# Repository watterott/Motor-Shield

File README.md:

# Motor-Shield
Shield for Arduino to drive DC-Motors, Solenoids or Relays.

* Compatible with [Arduino Motor-Shield](https://www.arduino.cc/en/Main/ArduinoMotorShieldR3)
* ST L298 Dual Full-Bridge Driver (2A per channel or 4A max)
* Open-Source and released under the [Creative Commons Attribution Share-Alike License](https://creativecommons.org/licenses/by-sa/4.0/).
* **[Documentation on learn.watterott.com](https://learn.watterott.com)**

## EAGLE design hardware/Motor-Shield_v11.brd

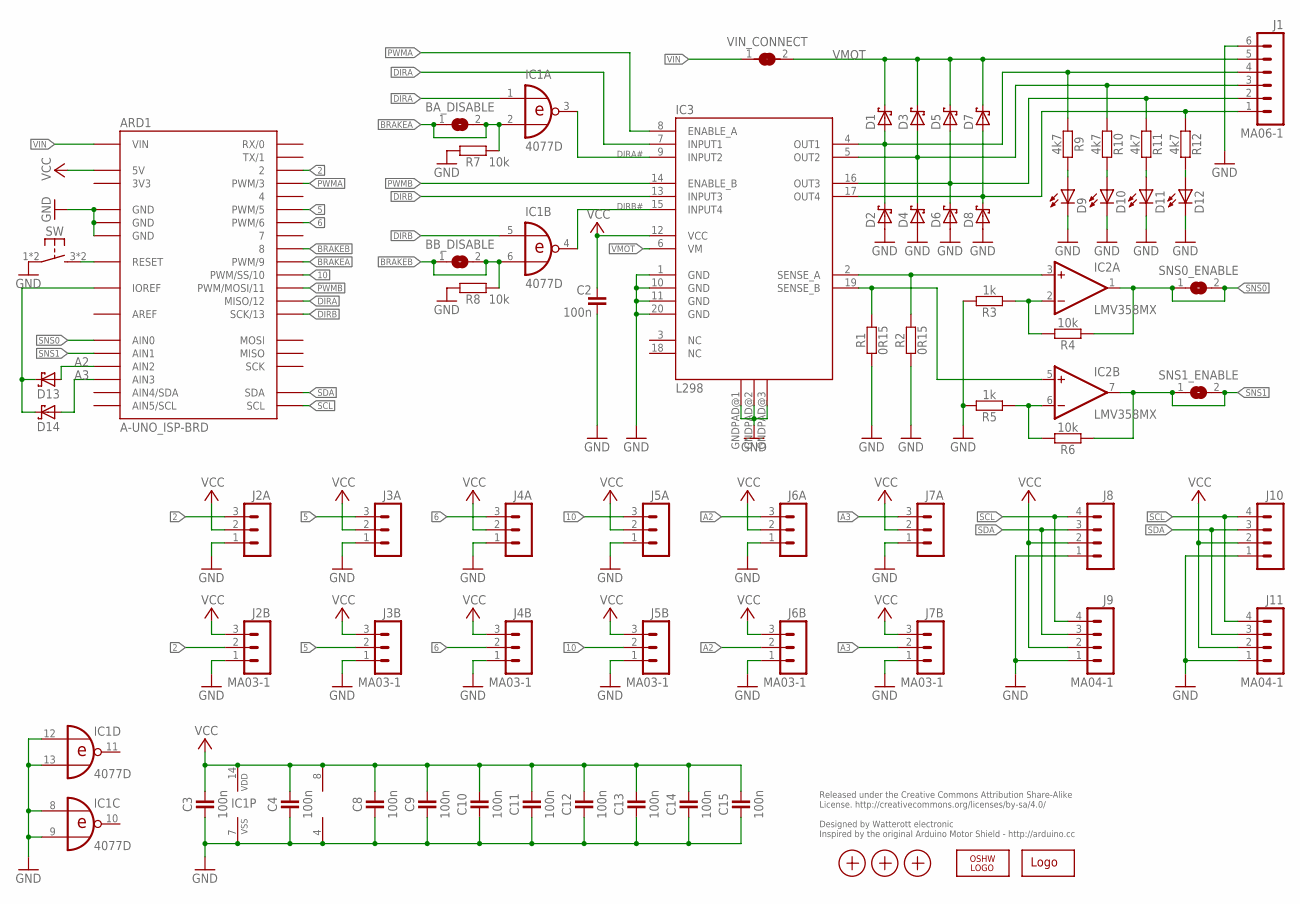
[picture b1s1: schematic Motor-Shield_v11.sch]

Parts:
ARD1: A-UNO_ISP-BRD; A-UNO-ISP
BA_DISABLE: JUMPER2-0603
BB_DISABLE: JUMPER2-0603
C2, C3, C4, C8, C9, C10, C11, C12, C13, C14, C15: 100n; C0402
D1, D2, D3, D4, D5, D6, D7, D8: D_SS14; DO214AC
D9, D10, D11, D12: LED-0603; C0603
D13, D14: D_SCHOTTKY-SOD110; SOD110
IC1: 4077D; SO14
IC2: LMV358MX; SO08
IC3: L298; POWERSO20
J1: MA06-1
J2A, J3A, J4A, J5A, J6A, J7A: JST_PH_3B3B-PH-SM4-TB; JST_B3B-PH-SM4-TB
J2B, J3B, J4B, J5B, J6B, J7B: MA03-1
J8, J10: JST_PH_4B4B-PH-SM4-TB; JST_B4B-PH-SM4-TB
J9, J11: MA04-1
LOGO1: LOGO-S_PLACE_S; SPARK_TPLACE_S
LOGO2: OSHW_LOGOX0070; OSHW_6X70
R1, R2: 0R15; C1206
R3, R5: 1k; C0402
R4, R6, R7, R8: 10k; C0402
R9, R10, R11, R12: 4k7; C0402
SNS0_ENABLE, SNS1_ENABLE: JUMPER2-0603
SW: SW-TACTILE-6X6_SMD; SW6X6_SMD
VIN_CONNECT: JUMPER2-0603
X1, X2, X3: PASSER-07; PASSER_07MM

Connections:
2: ARD1.2, J2A.3, J2B.2
3V3: ARD1.3V3
5: ARD1.5 (PWM/5), J3A.3, J3B.2
6: ARD1.6 (PWM/6), J4A.3, J4B.2
10: ARD1.10 (PWM/SS/10), J5A.3, J5B.2
A2: ARD1.A2 (AIN2), D13.A, J6A.3, J6B.2
A3: ARD1.A3 (AIN3), D14.A, J7A.3, J7B.2
AREF: ARD1.AREF
BRAKEA: ARD1.9 (PWM/9), BA_DISABLE.1, BA_DISABLE.2, IC1.2 (I1), R7.1
BRAKEB: ARD1.8, BB_DISABLE.1, BB_DISABLE.2, IC1.6 (I1), R8.1
DIRA: ARD1.12 (MISO/12), IC1.1 (I0), IC3.7 (INPUT1)
DIRA#: IC1.3 (O), IC3.9 (INPUT2)
DIRB: ARD1.13 (SCK/13), IC1.5 (I0), IC3.13 (INPUT3)
DIRB#: IC1.4 (O), IC3.15 (INPUT4)
GND: ARD1.GND@1 (GND), ARD1.GND@2 (GND), ARD1.GND@3 (GND), ARD1.GND@4 (GND), C2.1, C3.1, C4.1, C8.1, C9.1, C10.1, C11.1, C12.1, C13.1, C14.1, C15.1, D2.1 (A), D4.1 (A), D6.1 (A), D8.1 (A), D9.C, D10.C, D11.C, D12.C, IC1.7 (VSS), IC1.8 (I0), IC1.9 (I1), IC1.12 (I0), IC1.13 (I1), IC2.4 (V-), IC3.1 (GND), IC3.10 (GND), IC3.11 (GND), IC3.20 (GND), IC3.GNDPAD@1 (GNDPAD), IC3.GNDPAD@2 (GNDPAD), IC3.GNDPAD@3 (GNDPAD), J1.6, J2A.1, J2B.1, J3A.1, J3B.1, J4A.1, J4B.1, J5A.1, J5B.1, J6A.1, J6B.1, J7A.1, J7B.1, J8.1, J9.1, J10.1, J11.1, R1.1, R2.1, R3.2, R5.2, R7.2, R8.2, SW.1, SW.2 (P1)
IOREF: ARD1.IOREF, D13.C, D14.C
unnamed: D9.A, R9.2
unnamed: D10.A, R10.2
unnamed: IC2.2 (-IN), R3.1, R4.2
unnamed: IC2.6 (-IN), R5.1, R6.2
unnamed: D11.A, R11.2
unnamed: D12.A, R12.2
unnamed: ARD1.RST@1 (RESET), ARD1.RST@2 (RESET), SW.3 (S1), SW.4 (S1)
OUT1: D1.1 (A), D2.2 (C), IC3.4 (OUT1), J1.4, R9.1
OUT2: D3.1 (A), D4.2 (C), IC3.5 (OUT2), J1.3, R10.1
OUT3: D5.1 (A), D6.2 (C), IC3.16 (OUT3), J1.2, R11.1
OUT4: D7.1 (A), D8.2 (C), IC3.17 (OUT4), J1.1, R12.1
PWMA: ARD1.3 (PWM/3), IC3.8 (ENABLE_A)
PWMB: ARD1.11 (PWM/MOSI/11), IC3.14 (ENABLE_B)
SCL: ARD1.SCL, J8.4, J9.4, J10.4, J11.4
SDA: ARD1.SDA, J8.3, J9.3, J10.3, J11.3
SENSE_A: IC2.3 (+IN), IC3.2 (SENSE_A), R2.2
SENSE_B: IC2.5 (+IN), IC3.19 (SENSE_B), R1.2
SNS0: ARD1.A0 (AIN0), IC2.1 (OUT), R4.1, SNS0_ENABLE.1, SNS0_ENABLE.2
SNS1: ARD1.A1 (AIN1), IC2.7 (OUT), R6.1, SNS1_ENABLE.1, SNS1_ENABLE.2
VCC: ARD1.5V, ARD1.VCC (5V), C2.2, C3.2, C4.2, C8.2, C9.2, C10.2, C11.2, C12.2, C13.2, C14.2, C15.2, IC1.14 (VDD), IC2.8 (V+), IC3.12 (VCC), J2A.2, J2B.3, J3A.2, J3B.3, J4A.2, J4B.3, J5A.2, J5B.3, J6A.2, J6B.3, J7A.2, J7B.3, J8.2, J9.2, J10.2, J11.2
VIN: ARD1.VIN, VIN_CONNECT.1
VMOT: D1.2 (C), D3.2 (C), D5.2 (C), D7.2 (C), IC3.6 (VM), J1.5, VIN_CONNECT.2

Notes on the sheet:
Released under the Creative Commons Attribution Share-Alike License. http://creativecommons.org/licenses/by-sa/4.0/ Designed by Watterott electronic Inspired by the original Arduino Motor Shield - http://arduino.cc

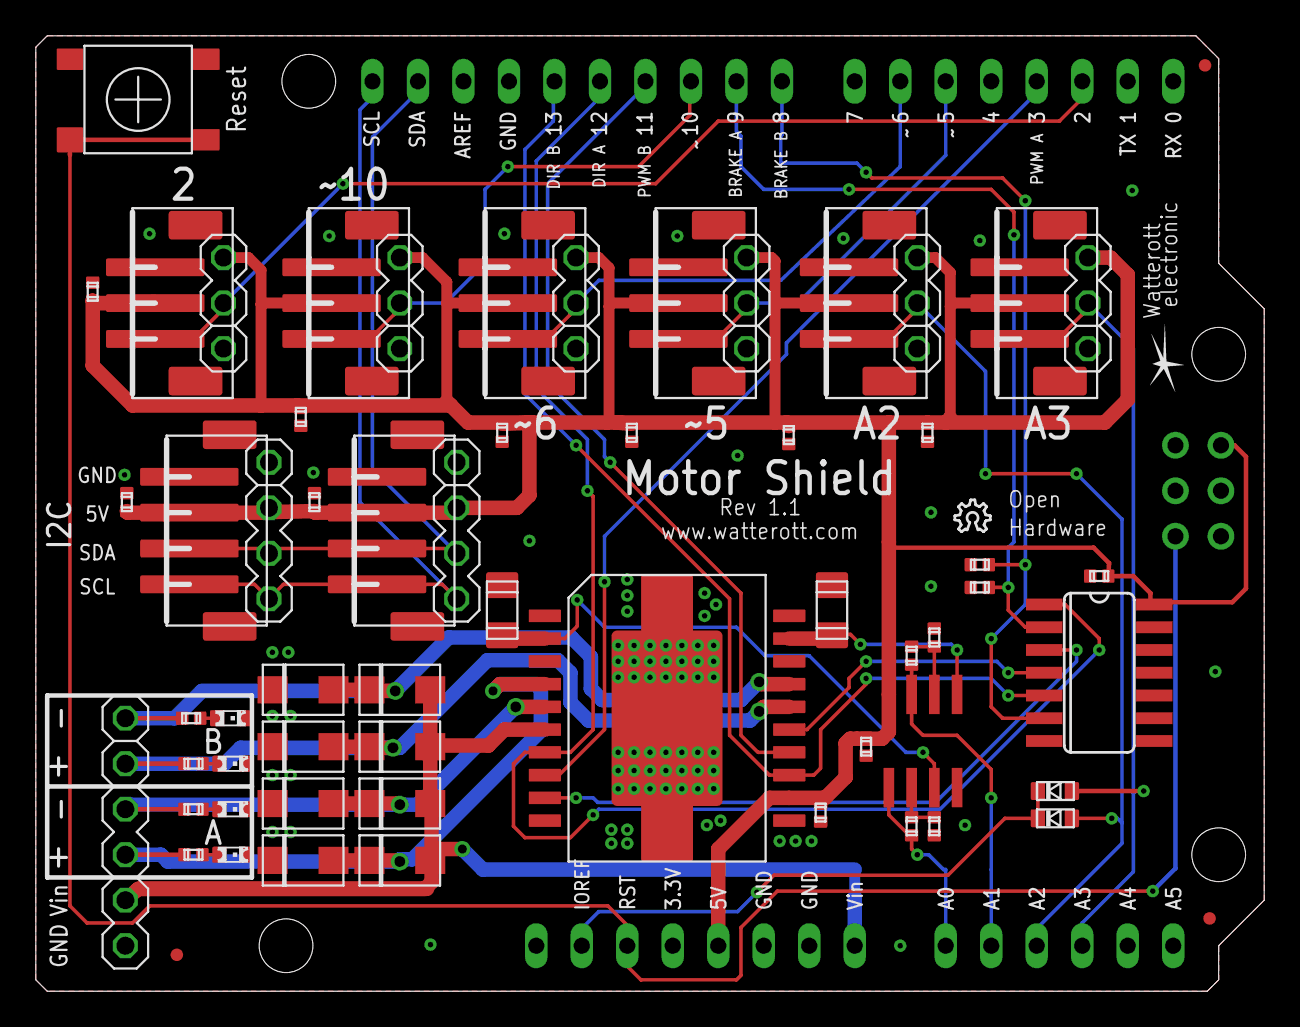
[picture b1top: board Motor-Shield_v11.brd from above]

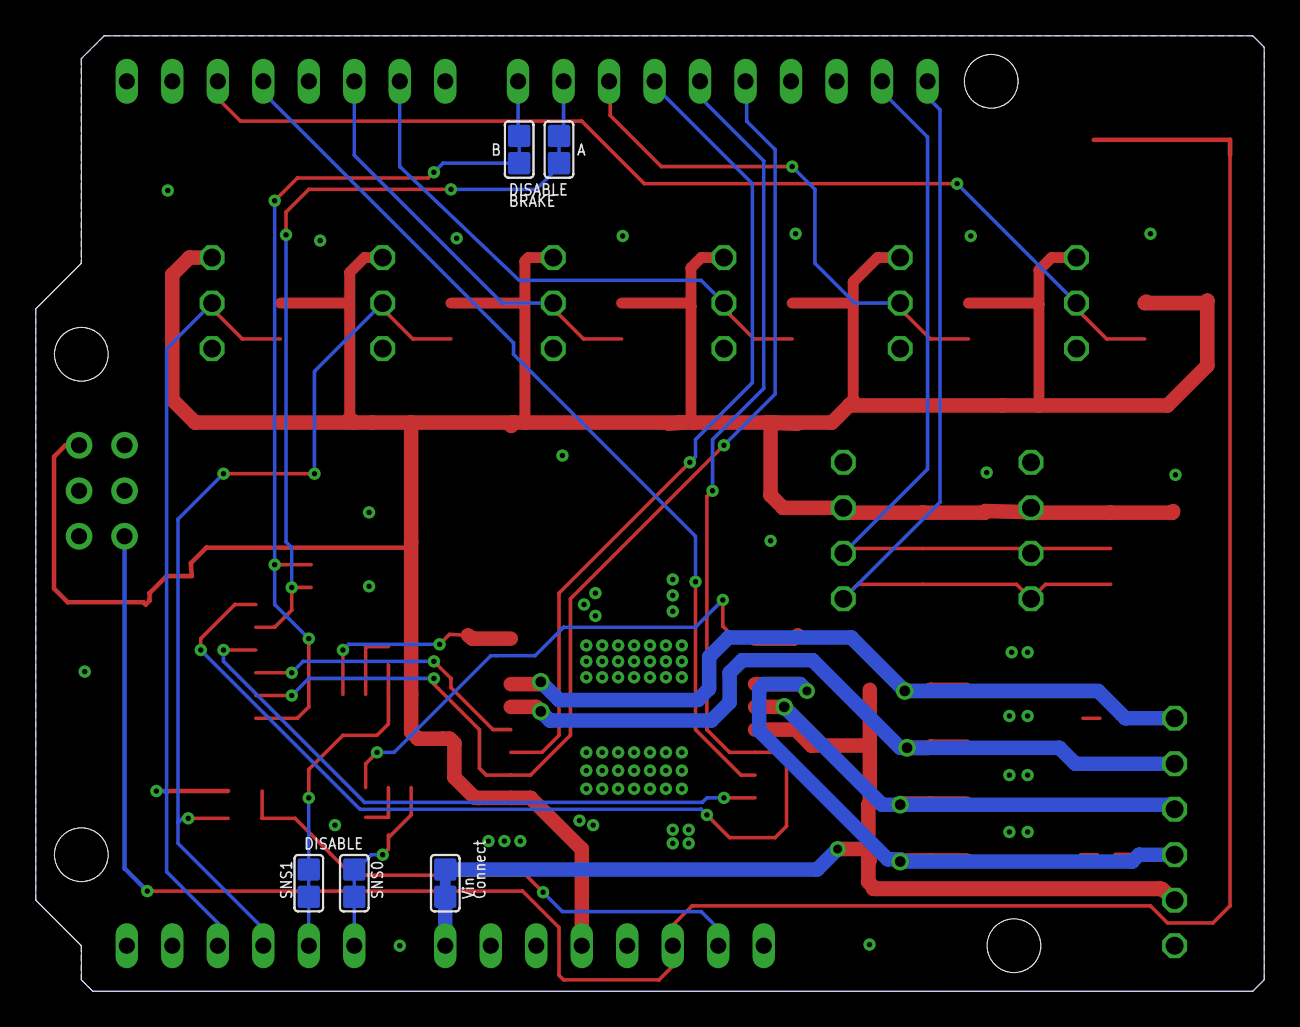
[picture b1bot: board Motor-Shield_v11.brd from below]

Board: 2 copper layers, 68.6 x 53.3 mm, 69 parts (5 on the bottom side), 36 nets.
